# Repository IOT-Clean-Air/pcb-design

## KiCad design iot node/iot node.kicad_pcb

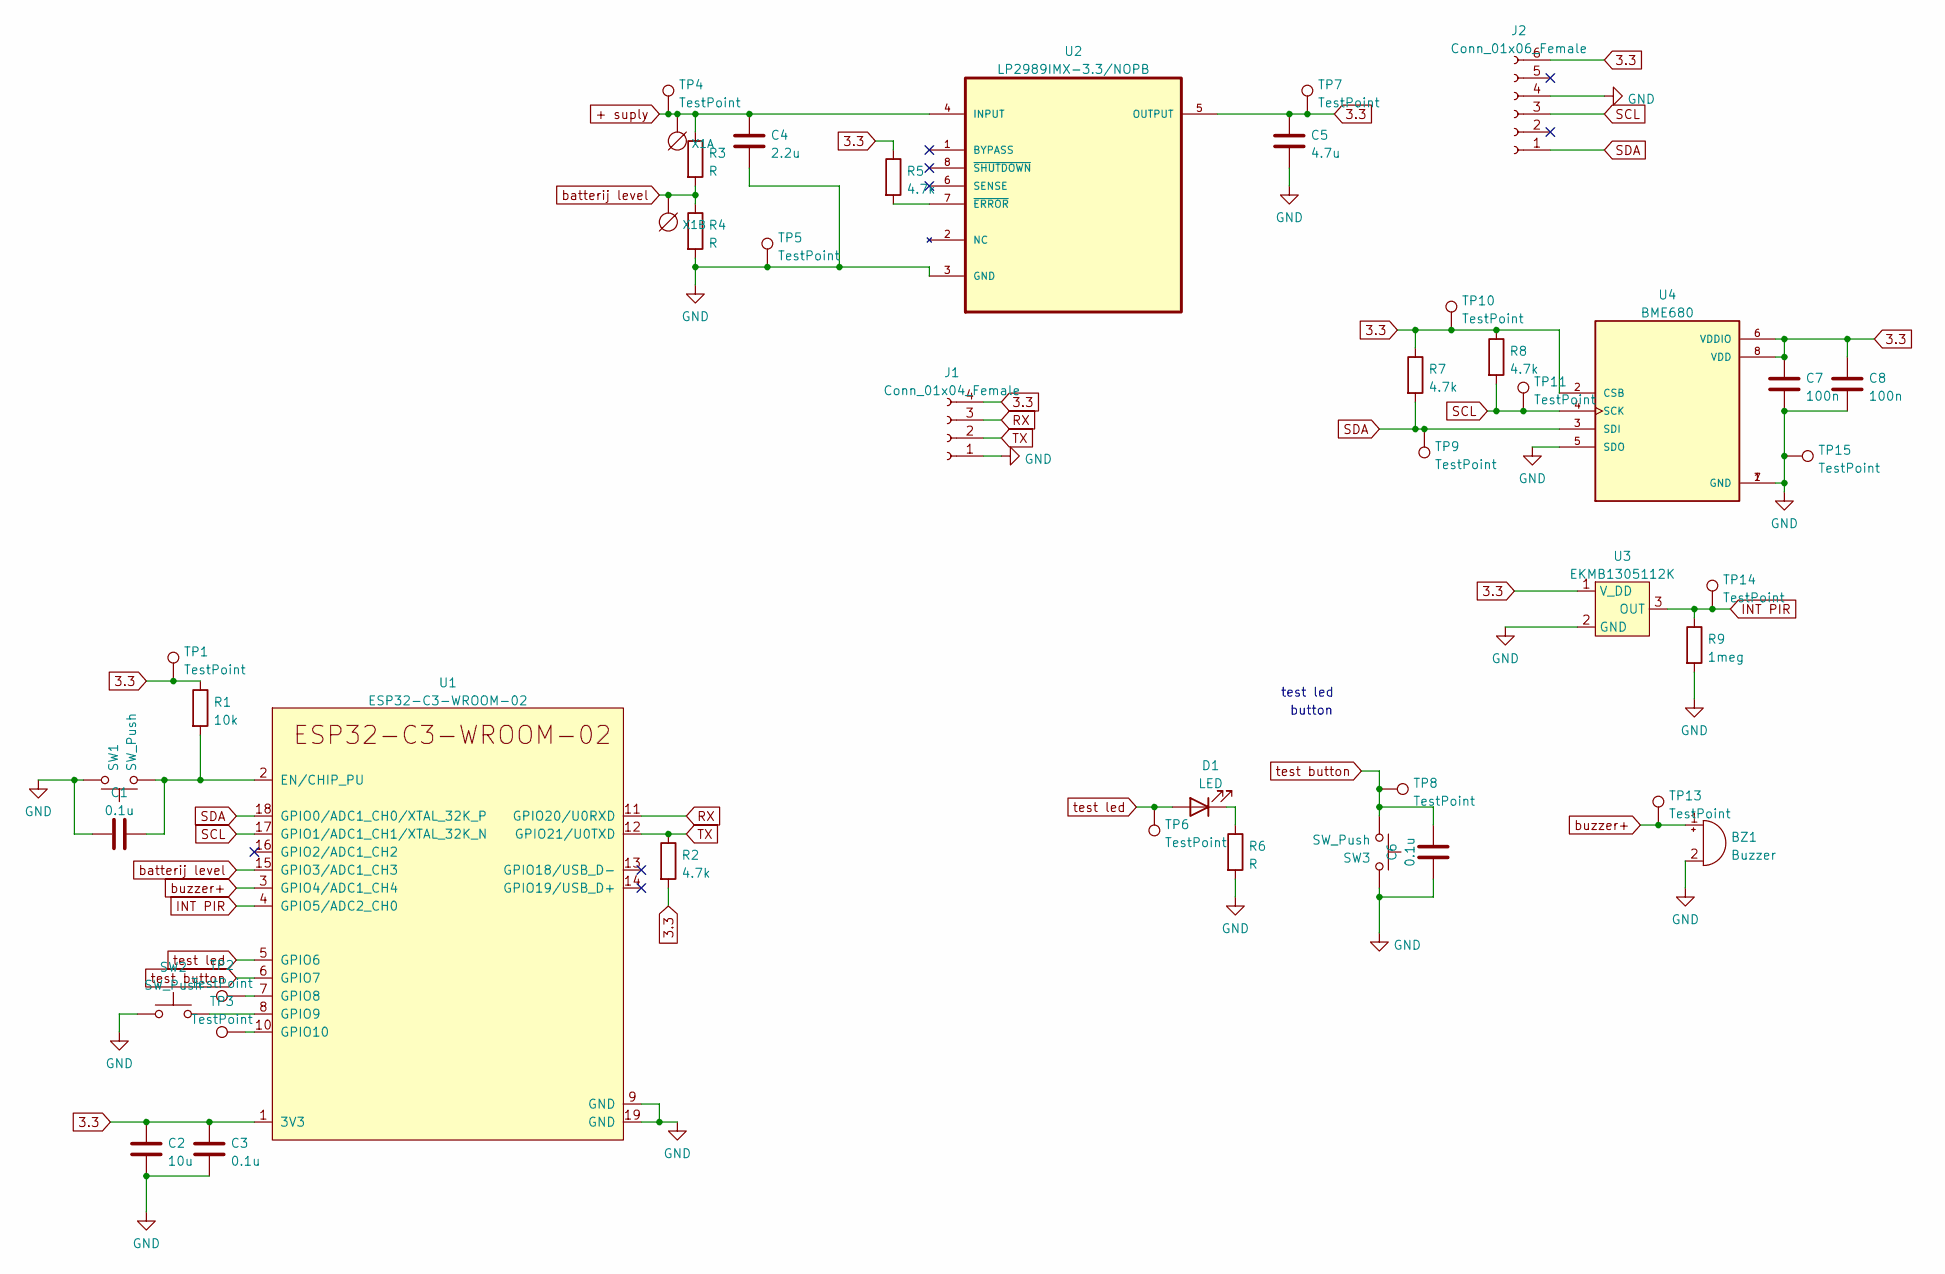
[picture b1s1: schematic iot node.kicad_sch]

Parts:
BZ1: Buzzer; AX1203DLF
C1, C3, C6: 0.1u; C_0805_2012Metric_Pad1.18x1.45mm_HandSolder
C2: 10u; C_0805_2012Metric_Pad1.18x1.45mm_HandSolder
C4: 2.2u; C_0805_2012Metric_Pad1.18x1.45mm_HandSolder
C5: 4.7u; C_0805_2012Metric_Pad1.18x1.45mm_HandSolder
C7, C8: 100n; C_0805_2012Metric_Pad1.18x1.45mm_HandSolder
D1: LED; LED_0805_2012Metric_Pad1.15x1.40mm_HandSolder
J1: Conn_01x04_Female; PinSocket_1x04_P2.54mm_Vertical
J2: Conn_01x06_Female; PinSocket_1x06_P2.54mm_Vertical
R1: 10k; R_0805_2012Metric_Pad1.20x1.40mm_HandSolder
R2, R5, R7, R8: 4.7k; R_0805_2012Metric_Pad1.20x1.40mm_HandSolder
R3, R4, R6: R; R_0805_2012Metric_Pad1.20x1.40mm_HandSolder
R9: 1meg; R_0805_2012Metric_Pad1.20x1.40mm_HandSolder
SW1, SW2, SW3: SW_Push; 434111043826
TP1, TP2, TP3, TP4, TP5, TP6, TP7, TP8, TP9, TP10, TP11, TP13, TP14, TP15: TestPoint; Pin_D0.7mm_L6.5mm_W1.8mm_FlatFork
U1: ESP32-C3-WROOM-02
U2: LP2989IMX-3.3/NOPB; SOIC127P600X175-8N; MPN LP2989IMX-3.3/NOPB
U3: EKMB1305112K
U4: BME680; PSON80P300X300X100-8N; PARTREV 1.0
X1: DG3XX-02-5.0; degson-DG306-5.0-02P

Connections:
3.3: C2.1, C3.1, C5.2, C7.1, C8.2, J1.4, J2.6, R1.1, R2.2, R5.1, R7.1, R8.1, TP1.1, TP7.1, TP10.1, U1.1 (3V3), U2.5 (OUTPUT), U3.1 (V_DD), U4.2 (CSB), U4.6 (VDDIO), U4.8 (VDD)
+ suply: C4.2, R3.1, TP4.1, U2.4 (INPUT), X1.1 (KL)
GND: BZ1.2 (+), C1.1, C2.2, C3.2, C4.1, C5.1, C6.1, C7.2, C8.1, J1.1, J2.4, R4.2, R6.2, R9.2, SW1.2, SW2.1, SW3.2, TP5.1, TP15.1, U1.9 (GND), U1.19 (GND), U2.3 (GND), U3.2 (GND), U4.1 (GND), U4.5 (SDO), U4.7 (GND)
INT PIR: R9.1, TP14.1, U1.4 (GPIO5/ADC2_CH0), U3.3 (OUT)
unnamed: C1.2, R1.2, SW1.1, U1.2 (EN/CHIP_PU)
unnamed: D1.1 (K), R6.1
unnamed: R5.2, U2.7 (~ERROR)
unnamed: SW2.2, U1.8 (GPIO9)
unnamed: TP2.1, U1.7 (GPIO8)
unnamed: TP3.1, U1.10 (GPIO10)
RX: J1.3, U1.11 (GPIO20/U0RXD)
SCL: J2.3, R8.2, TP11.1, U1.17 (GPIO1/ADC1_CH1/XTAL_32K_N), U4.4 (SCK)
SDA: J2.1, R7.2, TP9.1, U1.18 (GPIO0/ADC1_CH0/XTAL_32K_P), U4.3 (SDI)
TX: J1.2, R2.1, U1.12 (GPIO21/U0TXD)
batterij level: R3.2, R4.1, U1.15 (GPIO3/ADC1_CH3), X1.2 (KL)
buzzer+: BZ1.1 (-), TP13.1, U1.3 (GPIO4/ADC1_CH4)
test button: C6.2, SW3.1, TP8.1, U1.6 (GPIO7)
test led: D1.2 (A), TP6.1, U1.5 (GPIO6)

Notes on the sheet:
test led
button

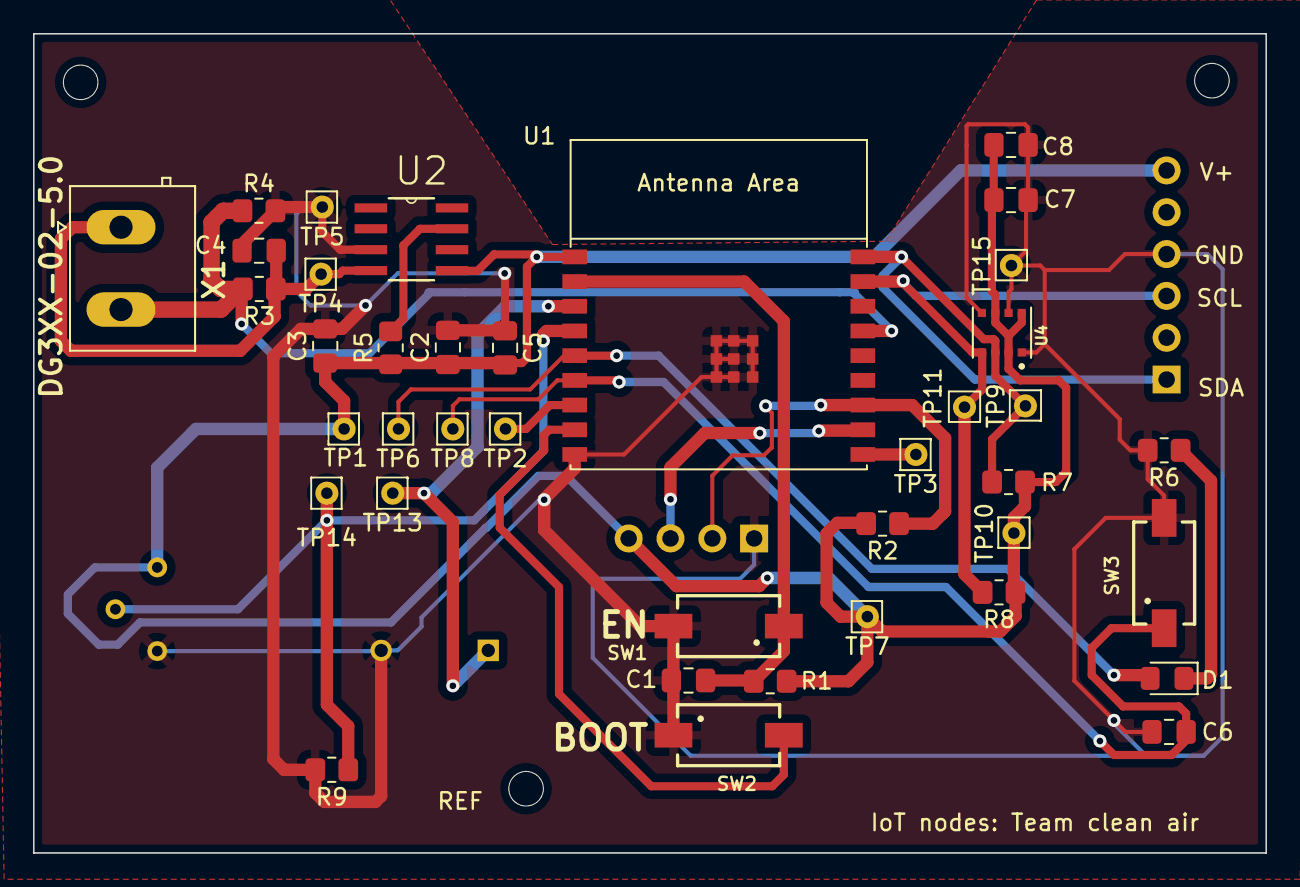
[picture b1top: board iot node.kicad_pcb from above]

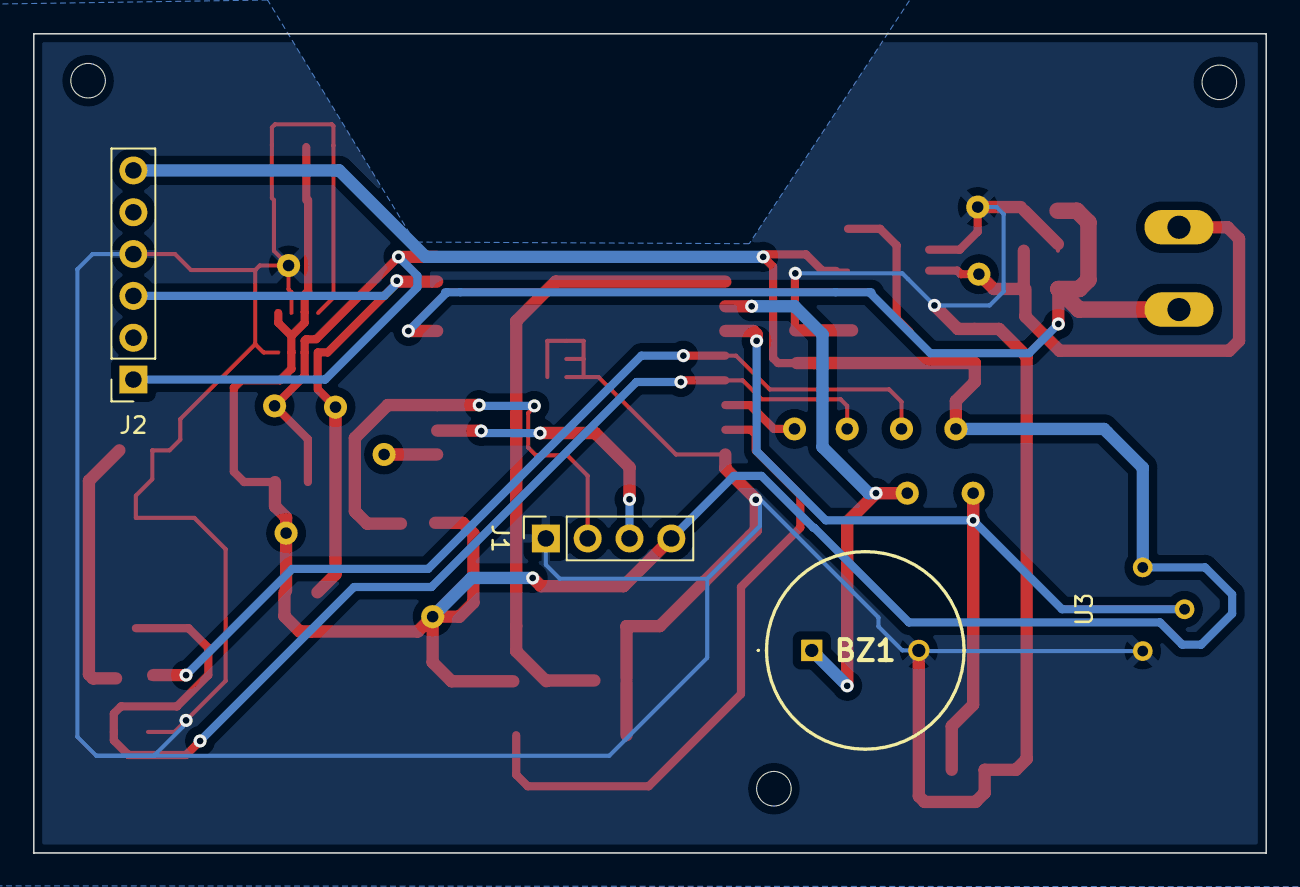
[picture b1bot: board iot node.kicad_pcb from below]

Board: 2 copper layers, 74.8 x 49.8 mm, 46 parts (4 on the bottom side), 18 nets.

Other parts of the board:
 : MountingHole_2.1mm
 #2: MountingHole_2.1mm
REF: MountingHole_2.1mm

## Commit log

2022-03-11 eerste versie
2022-03-15 new file
2022-03-15 update tekst
2022-03-17 versie voor 2de sessie
2022-03-18 esp32 c3 bevesteging
2022-03-18 sessie 2
2022-03-18 versie 2 sessie2
2022-03-18 Eerste PCB
2022-03-18 voltage suply adapt
2022-04-01 pcb gerber
